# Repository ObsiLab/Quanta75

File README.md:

# Quanta75 Mechanical Keyboard - 75% ISO Layout
Playing around trying to design a custom keyboard  

#### Project advancement : [Quanta75's Github Project](https://github.com/orgs/ObsiLab/projects/2)  

## Documentation
Documentation about Quanta75 can be found on [the Quanta website: quanta.obsilab.com](https://quanta.obsilab.com).

## PCB
Quanta75 exists in multiple versions:
- RP2040 Stamp microcontroller board by Solder Party
  - General components
  - JLCPCB assembly service optimized BOM
- RPi Pico microcontroller board
  - General components
  - JLCPCB assembly service optimized components
- Bare RP2040 microcontroller chip
  - General components
  - JLCPCB assembly service optimized components

All of them are using SMD components but no smaller than 0603 and on hand-solderable pads (a complete through-hole PCB could be coming next 👀). A PCB assembly service is still recommended.

#### See the PCB and schematic in [KiCanvas' Browser PCB viewer](https://kicanvas.org/?github=https%3A%2F%2Fgithub.com%2FLucasPlacentino%2FQuanta%2Ftree%2Fmain%2FQuanta_RP2040Stamp_JLCPCBAoptimized).

## Firmware (_WIP_)

[rmk_firmware](https://github.com/ObsiLab/rmk_firmware) _WIP_  
RMK is a keyboard firmware written in Rust, inspired by QMK or KMK. Originally built for the Quanta.

QMK config for the Quanta: _WIP_  

VIA config for the Quanta: _WIP_  

VIAL config for the Quanta: _WIP_  

## Design :
See the design details [here](/design).

## License
Project licensed under [CERN-OHL-P v2](LICENSE).

> Logos are licensed under [CC BY-NC-ND 4.0 ](https://creativecommons.org/licenses/by-nc-nd/4.0/) (more info [here](/design/README.md)).

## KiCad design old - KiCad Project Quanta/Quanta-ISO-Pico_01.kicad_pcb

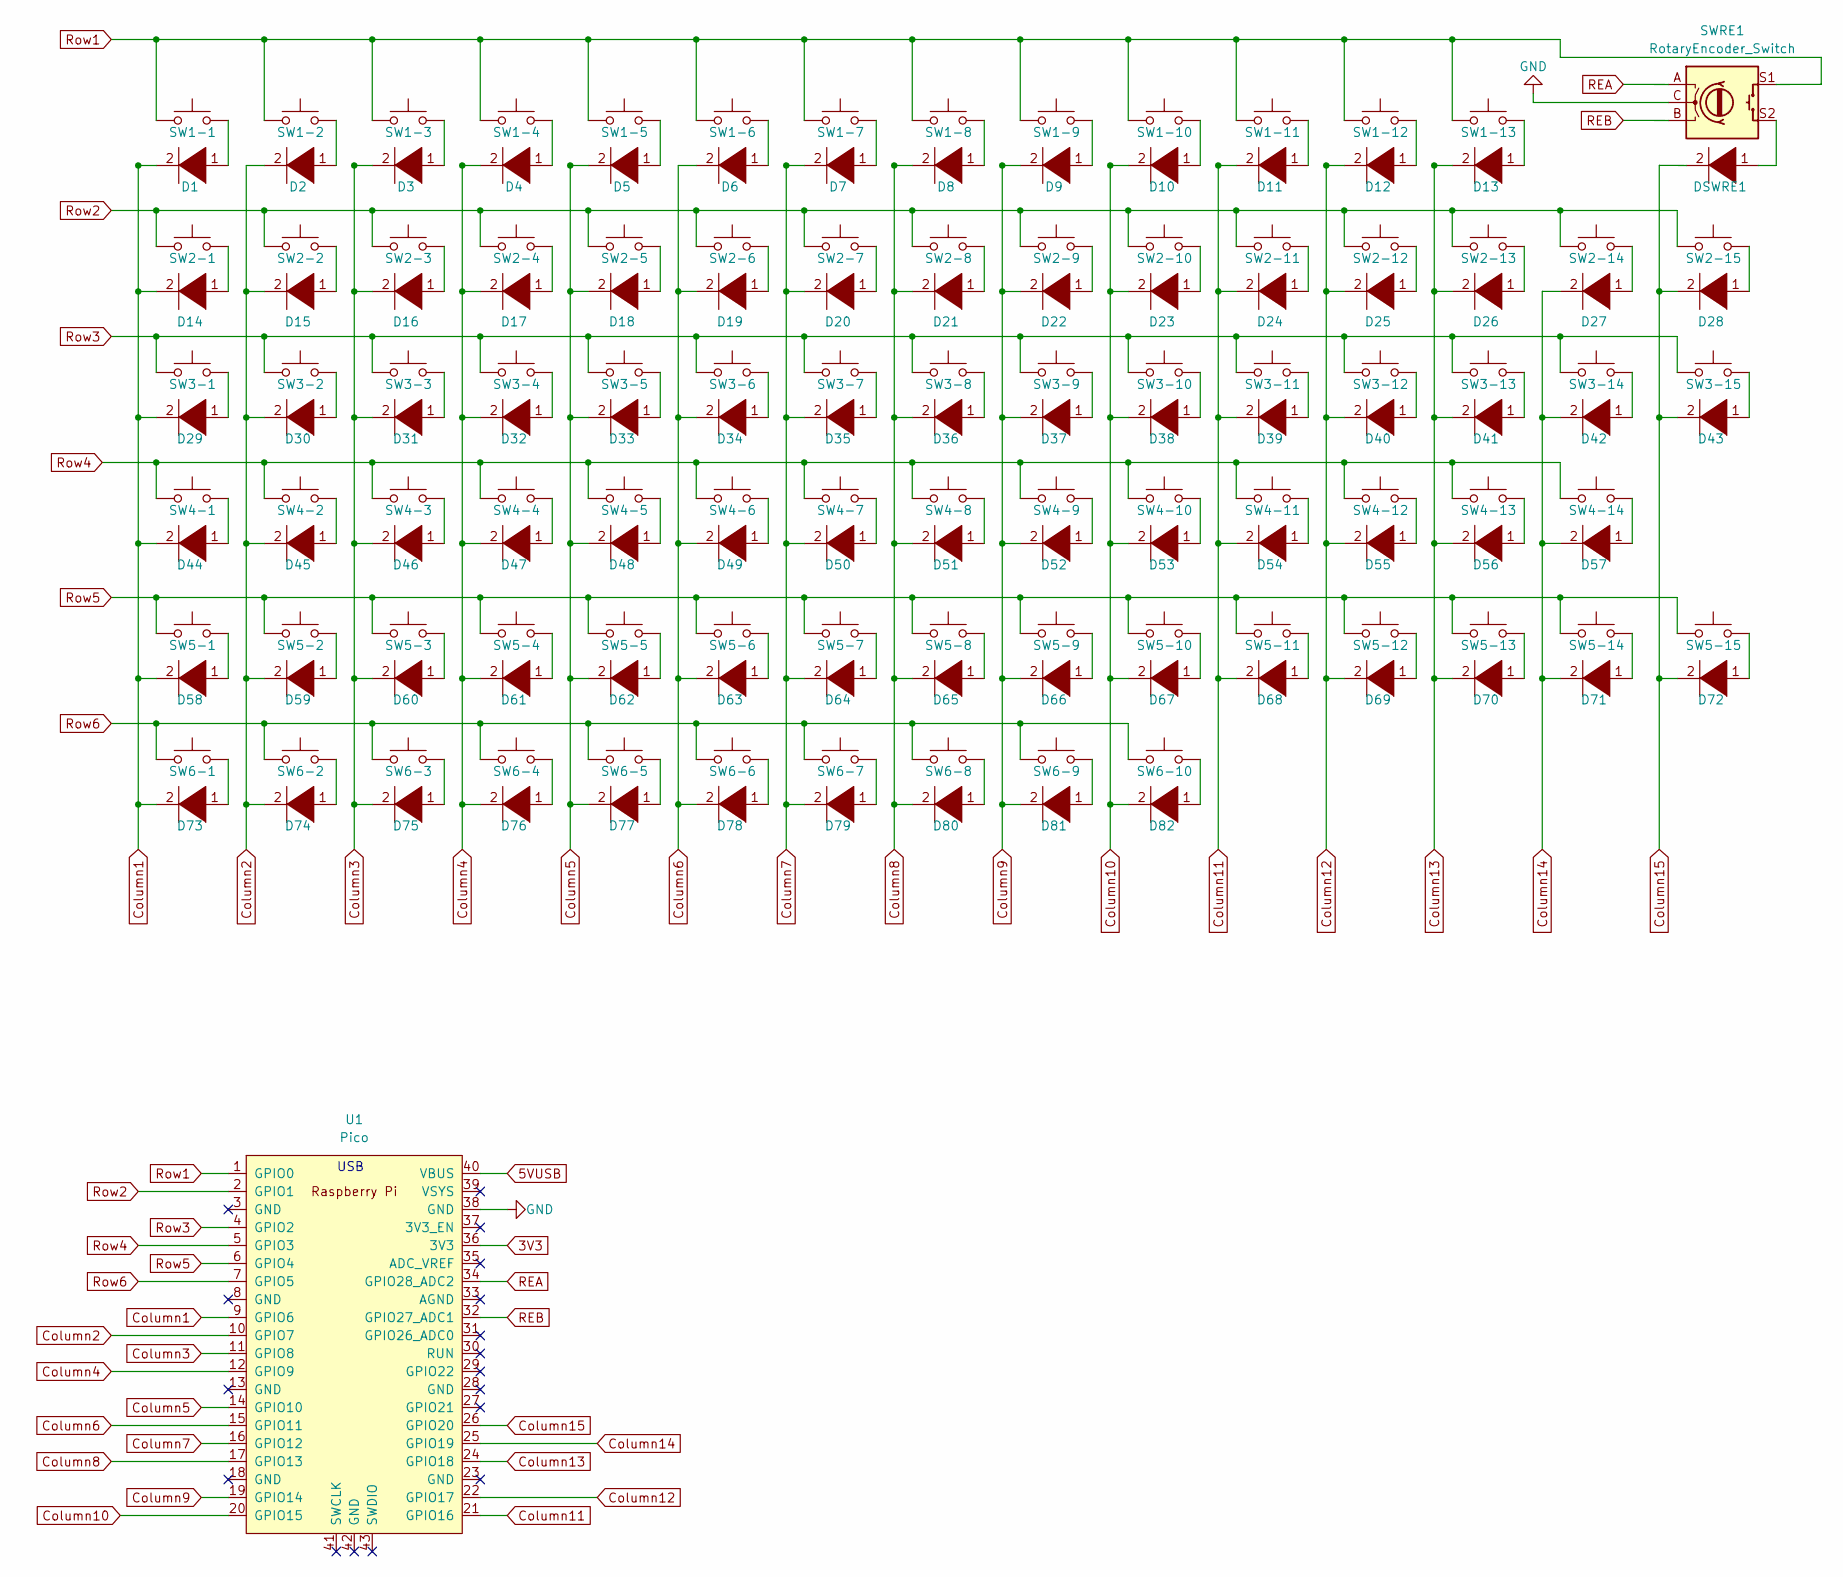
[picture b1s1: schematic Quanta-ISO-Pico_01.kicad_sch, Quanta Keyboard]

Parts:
D1, D2, D3, D4, D5, D6, D7, D8, D9, D10, D11, D12, D13, D14, D15, D16, D17, D18, D19, D20, D21, D22, D23, D24, D25, D26, D27, D28, D29, D30, D31, D32, D33, D34, D35, D36, D37, D38, D39, D40, D41, D42, D43, D44, D45, D46, D47, D48, D49, D50, D51, D52, D53, D54, D55, D56, D57, D58, D59, D60, D61, D62, D63, D64, D65, D66, D67, D68, D69, D70, D71, D72, D73, D74, D75, D76, D77, D78, D79, D80, D81, D82: DIODE; D_A-405_P7.62mm_Horizontal
DSWRE1: DIODE; D_A-405_P7.62mm_Horizontal
SW1-1, SW1-2, SW1-3, SW1-4, SW1-5, SW1-6, SW1-7, SW1-8, SW1-9, SW1-10, SW1-11, SW1-12, SW1-13, SW2-1, SW2-2, SW2-3, SW2-4, SW2-5, SW2-6, SW2-7, SW2-8, SW2-9, SW2-10, SW2-11, SW2-12, SW2-13, SW2-14, SW2-15, SW3-1, SW3-2, SW3-3, SW3-4, SW3-5, SW3-6, SW3-7, SW3-8, SW3-9, SW3-10, SW3-11, SW3-12, SW3-13, SW3-14, SW3-15, SW4-1, SW4-2, SW4-3, SW4-4, SW4-5, SW4-6, SW4-7, SW4-8, SW4-9, SW4-10, SW4-11, SW4-12, SW4-13, SW4-14, SW5-1, SW5-2, SW5-3, SW5-4, SW5-5, SW5-6, SW5-7, SW5-8, SW5-9, SW5-10, SW5-11, SW5-12, SW5-13, SW5-14, SW5-15, SW6-1, SW6-2, SW6-3, SW6-4, SW6-5, SW6-6, SW6-7, SW6-8, SW6-9, SW6-10: SW_Push; SW_Cherry_MX_1.00u_PCB
SWRE1: RotaryEncoder_Switch; RotaryEncoder_Bourns_Vertical_PEC12R-3xxxF-Sxxxx
U1: Pico; RPi_Pico_SMD_TH

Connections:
Column1: D1.2 (A), D14.2 (A), D29.2 (A), D44.2 (A), D58.2 (A), D73.2 (A), U1.9 (GPIO6)
Column2: D2.2 (A), D15.2 (A), D30.2 (A), D45.2 (A), D59.2 (A), D74.2 (A), U1.10 (GPIO7)
Column3: D3.2 (A), D16.2 (A), D31.2 (A), D46.2 (A), D60.2 (A), D75.2 (A), U1.11 (GPIO8)
Column4: D4.2 (A), D17.2 (A), D32.2 (A), D47.2 (A), D61.2 (A), D76.2 (A), U1.12 (GPIO9)
Column5: D5.2 (A), D18.2 (A), D33.2 (A), D48.2 (A), D62.2 (A), D77.2 (A), U1.14 (GPIO10)
Column6: D6.2 (A), D19.2 (A), D34.2 (A), D49.2 (A), D63.2 (A), D78.2 (A), U1.15 (GPIO11)
Column7: D7.2 (A), D20.2 (A), D35.2 (A), D50.2 (A), D64.2 (A), D79.2 (A), U1.16 (GPIO12)
Column8: D8.2 (A), D21.2 (A), D36.2 (A), D51.2 (A), D65.2 (A), D80.2 (A), U1.17 (GPIO13)
Column9: D9.2 (A), D22.2 (A), D37.2 (A), D52.2 (A), D66.2 (A), D81.2 (A), U1.19 (GPIO14)
Column10: D10.2 (A), D23.2 (A), D38.2 (A), D53.2 (A), D67.2 (A), D82.2 (A), U1.20 (GPIO15)
Column11: D11.2 (A), D24.2 (A), D39.2 (A), D54.2 (A), D68.2 (A), U1.21 (GPIO16)
Column12: D12.2 (A), D25.2 (A), D40.2 (A), D55.2 (A), D69.2 (A), U1.22 (GPIO17)
Column13: D13.2 (A), D26.2 (A), D41.2 (A), D56.2 (A), D70.2 (A), U1.24 (GPIO18)
Column14: D27.2 (A), D42.2 (A), D57.2 (A), D71.2 (A), U1.25 (GPIO19)
Column15: D28.2 (A), D43.2 (A), D72.2 (A), DSWRE1.2 (A), U1.26 (GPIO20)
GND: SWRE1.C, U1.38 (GND)
unnamed: D1.1 (K), SW1-1.2
unnamed: D2.1 (K), SW1-2.2
unnamed: D3.1 (K), SW1-3.2
unnamed: D4.1 (K), SW1-4.2
unnamed: D5.1 (K), SW1-5.2
unnamed: D6.1 (K), SW1-6.2
unnamed: D7.1 (K), SW1-7.2
unnamed: D8.1 (K), SW1-8.2
unnamed: D9.1 (K), SW1-9.2
unnamed: D10.1 (K), SW1-10.2
unnamed: D11.1 (K), SW1-11.2
unnamed: D12.1 (K), SW1-12.2
unnamed: D13.1 (K), SW1-13.2
unnamed: D14.1 (K), SW2-1.2
unnamed: D15.1 (K), SW2-2.2
unnamed: D16.1 (K), SW2-3.2
unnamed: D17.1 (K), SW2-4.2
unnamed: D18.1 (K), SW2-5.2
unnamed: D19.1 (K), SW2-6.2
unnamed: D20.1 (K), SW2-7.2
unnamed: D21.1 (K), SW2-8.2
unnamed: D22.1 (K), SW2-9.2
unnamed: D23.1 (K), SW2-10.2
unnamed: D24.1 (K), SW2-11.2
unnamed: D25.1 (K), SW2-12.2
unnamed: D26.1 (K), SW2-13.2
unnamed: D27.1 (K), SW2-14.2
unnamed: D28.1 (K), SW2-15.2
unnamed: D29.1 (K), SW3-1.2
unnamed: D30.1 (K), SW3-2.2
unnamed: D31.1 (K), SW3-3.2
unnamed: D32.1 (K), SW3-4.2
unnamed: D33.1 (K), SW3-5.2
unnamed: D34.1 (K), SW3-6.2
unnamed: D35.1 (K), SW3-7.2
unnamed: D36.1 (K), SW3-8.2
unnamed: D37.1 (K), SW3-9.2
unnamed: D38.1 (K), SW3-10.2
unnamed: D39.1 (K), SW3-11.2
unnamed: D40.1 (K), SW3-12.2
unnamed: D41.1 (K), SW3-13.2
unnamed: D42.1 (K), SW3-14.2
unnamed: D43.1 (K), SW3-15.2
unnamed: D44.1 (K), SW4-1.2
unnamed: D45.1 (K), SW4-2.2
unnamed: D46.1 (K), SW4-3.2
unnamed: D47.1 (K), SW4-4.2
unnamed: D48.1 (K), SW4-5.2
unnamed: D49.1 (K), SW4-6.2
unnamed: D50.1 (K), SW4-7.2
unnamed: D51.1 (K), SW4-8.2
unnamed: D52.1 (K), SW4-9.2
unnamed: D53.1 (K), SW4-10.2
unnamed: D54.1 (K), SW4-11.2
unnamed: D55.1 (K), SW4-12.2
unnamed: D56.1 (K), SW4-13.2
unnamed: D57.1 (K), SW4-14.2
unnamed: D58.1 (K), SW5-1.2
unnamed: D59.1 (K), SW5-2.2
unnamed: D60.1 (K), SW5-3.2
unnamed: D61.1 (K), SW5-4.2
unnamed: D62.1 (K), SW5-5.2
unnamed: D63.1 (K), SW5-6.2
unnamed: D64.1 (K), SW5-7.2
unnamed: D65.1 (K), SW5-8.2
unnamed: D66.1 (K), SW5-9.2
unnamed: D67.1 (K), SW5-10.2
unnamed: D68.1 (K), SW5-11.2
unnamed: D69.1 (K), SW5-12.2
unnamed: D70.1 (K), SW5-13.2
unnamed: D71.1 (K), SW5-14.2
unnamed: D72.1 (K), SW5-15.2
unnamed: D73.1 (K), SW6-1.2
unnamed: D74.1 (K), SW6-2.2
unnamed: D75.1 (K), SW6-3.2
unnamed: D76.1 (K), SW6-4.2
unnamed: D77.1 (K), SW6-5.2
unnamed: D78.1 (K), SW6-6.2
unnamed: D79.1 (K), SW6-7.2
unnamed: D80.1 (K), SW6-8.2
unnamed: D81.1 (K), SW6-9.2
unnamed: D82.1 (K), SW6-10.2
unnamed: DSWRE1.1 (K), SWRE1.S2
REA: SWRE1.A, U1.34 (GPIO28_ADC2)
REB: SWRE1.B, U1.32 (GPIO27_ADC1)
Row1: SW1-1.1, SW1-2.1, SW1-3.1, SW1-4.1, SW1-5.1, SW1-6.1, SW1-7.1, SW1-8.1, SW1-9.1, SW1-10.1, SW1-11.1, SW1-12.1, SW1-13.1, SWRE1.S1, U1.1 (GPIO0)
Row2: SW2-1.1, SW2-2.1, SW2-3.1, SW2-4.1, SW2-5.1, SW2-6.1, SW2-7.1, SW2-8.1, SW2-9.1, SW2-10.1, SW2-11.1, SW2-12.1, SW2-13.1, SW2-14.1, SW2-15.1, U1.2 (GPIO1)
Row3: SW3-1.1, SW3-2.1, SW3-3.1, SW3-4.1, SW3-5.1, SW3-6.1, SW3-7.1, SW3-8.1, SW3-9.1, SW3-10.1, SW3-11.1, SW3-12.1, SW3-13.1, SW3-14.1, SW3-15.1, U1.4 (GPIO2)
Row4: SW4-1.1, SW4-2.1, SW4-3.1, SW4-4.1, SW4-5.1, SW4-6.1, SW4-7.1, SW4-8.1, SW4-9.1, SW4-10.1, SW4-11.1, SW4-12.1, SW4-13.1, SW4-14.1, U1.5 (GPIO3)
Row5: SW5-1.1, SW5-2.1, SW5-3.1, SW5-4.1, SW5-5.1, SW5-6.1, SW5-7.1, SW5-8.1, SW5-9.1, SW5-10.1, SW5-11.1, SW5-12.1, SW5-13.1, SW5-14.1, SW5-15.1, U1.6 (GPIO4)
Row6: SW6-1.1, SW6-2.1, SW6-3.1, SW6-4.1, SW6-5.1, SW6-6.1, SW6-7.1, SW6-8.1, SW6-9.1, SW6-10.1, U1.7 (GPIO5)

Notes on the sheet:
USB

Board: 2 copper layers, 166 parts (0 on the bottom side), 104 nets, no tracks yet.

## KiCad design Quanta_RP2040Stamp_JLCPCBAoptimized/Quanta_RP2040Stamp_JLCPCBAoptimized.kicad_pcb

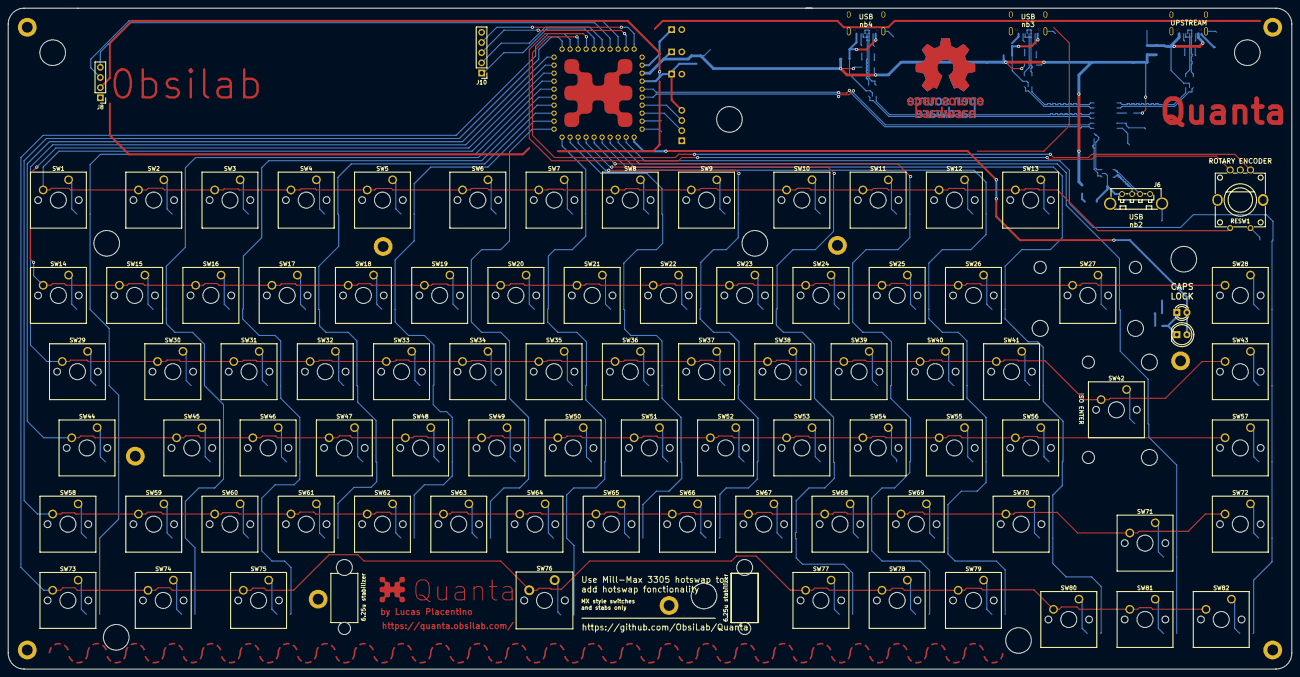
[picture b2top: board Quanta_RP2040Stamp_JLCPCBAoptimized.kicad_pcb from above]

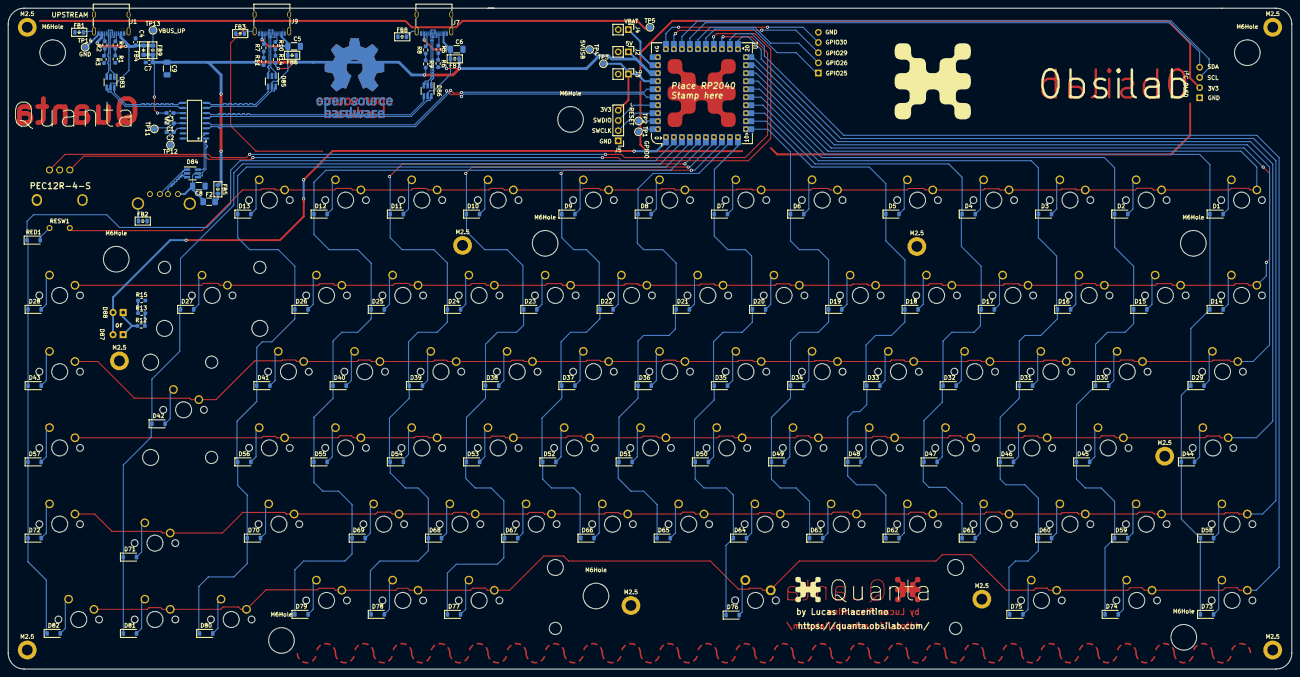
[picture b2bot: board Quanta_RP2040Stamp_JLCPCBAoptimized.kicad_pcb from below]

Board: 2 copper layers, 320.7 x 165.1 mm, 249 parts (140 on the bottom side), 162 nets.

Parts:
6.25u stabilizer: Stabilizer_Cherry_MX_6.25u
C1, C2, C4: 10uF; C_0603_1608Metric_Pad1.08x0.95mm_HandSolder
C3, C7: 100nF; C_0603_1608Metric_Pad1.08x0.95mm_HandSolder
C5, C6, C8, C9: 100uF; C_1206_3216Metric_Pad1.33x1.80mm_HandSolder
D1, D2, D3, D4, D5, D6, D7, D8, D9, D10, D11, D12, D13, D14, D15, D16, D17, D18, D19, D20, D21, D22, D23, D24, D25, D26, D27, D28, D29, D30, D31, D32, D33, D34, D35, D36, D37, D38, D39, D40, D41, D42, D43, D44, D45, D46, D47, D48, D49, D50, D51, D52, D53, D54, D55, D56, D57, D58, D59, D60, D61, D62, D63, D64, D65, D66, D67, D68, D69, D70, D71, D72, D73, D74, D75, D76, D77, D78, D79, D80, D81, D82: DIODE; D_SOD-123
D83, D84, D85, D86: USBLC6-2SC6; SOT-23-6_Handsoldering
D87: Amber LED; LED_D5.0mm_Clear
D88: Amber LED; LED_D3.0mm_Clear
F2: 500mA; Fuse_1206_3216Metric_Pad1.42x1.75mm_HandSolder
FB1, FB2, FB3, FB8: 600R; Ferrite_0805_2012Metric
FB4, FB9: 100R 800mA; Ferrite_0805_2012Metric_Pad1.05x1.20mm_BigPads
FB5, FB6, FB7: 600R 500mA; Ferrite_0805_2012Metric
J1, J7, J9: USB_C_Receptacle_USB2.0; USB-C-SMD_G-SWITCH_GT-USB-7010EN
J2: Conn_01x02_Socket VBUS 5V; PinHeader_1x02_P2.54mm_Vertical
J3: Conn_01x02_Socket 3V3; PinHeader_1x02_P2.54mm_Vertical
J4: Conn_01x02_Socket VBAT; PinHeader_1x02_P2.54mm_Vertical
J5: Conn_01x04_Socket SWD; PinHeader_1x04_P2.54mm_Vertical
J6: USB_A_Receptacle_UBS2.0; USB-A-TH_KH-AF180ZJ-13.7
J8: Conn_01x04_Socket I2C display; PinHeader_1x04_P2.54mm_Vertical
J10: Conn_01x05_Socket GPIOs; PinHeader_1x05_P2.54mm_Vertical
M2.5, M2.5#2, M2.5#3, M2.5#4, M2.5#5, M2.5#6, M2.5#7, M2.5#8, M2.5#9, M2.5#10: MountingHole_2.7mm_M2.5_DIN965_Pad
M6Hole, M6Hole#2, M6Hole#3, M6Hole#4, M6Hole#5, M6Hole#6, M6Hole#7, M6Hole#8, M6Hole#9: MountingHole_6.4mm_M6_DIN965
OSHW-logo: OSHW-Logo_19x20mm_Copper
Quanta***: LOGO; Quanta-logo
R1, R3, R12, R13, R15: 120R; R_0603_1608Metric_Pad0.98x0.95mm_HandSolder
R2, R4: 4k99; R_0603_1608Metric_Pad0.98x0.95mm_HandSolder
R5, R7, R8, R10: 43k; R_0603_1608Metric_Pad0.98x0.95mm_HandSolder
R6, R9, R11, R14: 15k; R_0603_1608Metric_Pad0.98x0.95mm_HandSolder
RED1: DIODE; D_SOD-123
RESW1: RotaryEncoder_Switch; SW-TH_PEC12R-4120F-S0012
SW1, SW2, SW3, SW4, SW5, SW6, SW7, SW8, SW9, SW10, SW11, SW12, SW13, SW14, SW15, SW16, SW17, SW18, SW19, SW20, SW21, SW22, SW23, SW24, SW25, SW26, SW28, SW30, SW31, SW32, SW33, SW34, SW35, SW36, SW37, SW38, SW39, SW40, SW41, SW43, SW45, SW46, SW47, SW48, SW49, SW50, SW51, SW52, SW53, SW54, SW55, SW56, SW57, SW59, SW60, SW61, SW62, SW63, SW64, SW65, SW66, SW67, SW68, SW69, SW71, SW72, SW77, SW78, SW79, SW80, SW81, SW82: SW_Push; SW_Cherry_MX_1.00u_PCB
SW27: SW_Push; SW_Cherry_MX_2.00u_PCB
SW29: SW_Push; SW_Cherry_MX_1.50u_PCB
SW42: SW_Push; SW_Cherry_MX_ISOEnter_PCB
SW44, SW70: SW_Push; SW_Cherry_MX_1.75u_PCB
SW58, SW73, SW74, SW75: SW_Push; SW_Cherry_MX_1.25u_PCB
SW76: SW_Push; SW_Cherry_MX_PCB_6.25u
TP1: BOOTSEL; TestPoint_Pad_D1.5mm
TP2: -RESET; TestPoint_Pad_D1.5mm
TP3: 3V3; TestPoint_Pad_D1.5mm
TP4: 5VUSB; TestPoint_Pad_D1.5mm
TP5, TP14: GND; TestPoint_Pad_D1.5mm
TP11: VDD3; TestPoint_Pad_D1.5mm
TP12: VDD18; TestPoint_Pad_D1.5mm
TP13: VBUS_UP; TestPoint_Pad_D1.5mm
U1: RP2040_Stamp; RP2040_Stamp_THT
U2: SL2.1A; SOP-16_L10.0-W3.9-P1.27-LS6.0-BL

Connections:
+3.3V: J3.1, J5.4, J8.2, TP3.1, U1.34 (3.3V)
+5V: C3.2, C7.2, C9.2, FB4.2, FB5.1, FB6.1, FB7.1, FB9.2, J2.1, R6.2, R9.2, R11.2, R14.2, TP4.1, U1.33 (5V)
/USB2+: D84.1 (L1), J6.3 (D+)
/USB2-: D84.3 (L2), J6.2 (D-)
/USB3+: D85.3 (L2), J9.A6 (D+), J9.B6 (D+)
/USB3-: D85.1 (L1), J9.A7 (D-), J9.B7 (D-)
/USB4+: D86.3 (L2), J7.A6 (D+), J7.B6 (D+)
/USB4-: D86.1 (L1), J7.A7 (D-), J7.B7 (D-)
/USBUP+: D83.4 (L2), U2.10 (DP)
/USBUP-: D83.6 (L1), U2.9 (DM)
Column1: D1.1 (K), D14.1 (K), D29.1 (K), D44.1 (K), D58.1 (K), D73.1 (K), U1.16 (GPIO15)
Column2: D2.1 (K), D15.1 (K), D30.1 (K), D45.1 (K), D59.1 (K), D74.1 (K), U1.15 (GPIO14)
Column3: D3.1 (K), D16.1 (K), D31.1 (K), D46.1 (K), D60.1 (K), D75.1 (K), U1.14 (GPIO13)
Column4: D4.1 (K), D17.1 (K), D32.1 (K), D47.1 (K), D61.1 (K), U1.13 (GPIO12)
Column5: D5.1 (K), D18.1 (K), D33.1 (K), D48.1 (K), D62.1 (K), U1.12 (GPIO11)
Column6: D6.1 (K), D19.1 (K), D34.1 (K), D49.1 (K), D63.1 (K), U1.11 (GPIO10)
Column7: D7.1 (K), D20.1 (K), D35.1 (K), D50.1 (K), D64.1 (K), D76.1 (K), U1.10 (GPIO9)
Column8: D8.1 (K), D21.1 (K), D36.1 (K), D51.1 (K), D65.1 (K), U1.9 (GPIO8)
Column9: D9.1 (K), D22.1 (K), D37.1 (K), D52.1 (K), D66.1 (K), U1.8 (GPIO7)
Column10: D10.1 (K), D23.1 (K), D38.1 (K), D53.1 (K), D67.1 (K), D77.1 (K), U1.7 (GPIO6)
Column11: D11.1 (K), D24.1 (K), D39.1 (K), D54.1 (K), D68.1 (K), D78.1 (K), U1.6 (GPIO5)
Column12: D12.1 (K), D25.1 (K), D40.1 (K), D55.1 (K), D69.1 (K), D79.1 (K), U1.5 (GPIO4)
Column13: D13.1 (K), D26.1 (K), D41.1 (K), D56.1 (K), D70.1 (K), D80.1 (K), U1.4 (GPIO3)
Column14: D27.1 (K), D42.1 (K), D71.1 (K), D81.1 (K), U1.3 (GPIO2)
Column15: D28.1 (K), D43.1 (K), D57.1 (K), D72.1 (K), D82.1 (K), RED1.1 (K), U1.2 (GPIO1)
GND: C1.2, C2.2, C4.1, C5.2, C6.2, C7.1, C8.1, C9.1, D83.2 (VN), D84.2 (VN), D85.2 (VN), D86.2 (VN), FB1.1, FB2.1, FB3.1, FB8.1, J1.A1 (GND), J1.B1 (GND), J2.2, J3.2, J4.2, J5.1, J6.4 (GND), J7.A1 (GND), J7.B1 (GND), J8.1, J9.A1 (GND), J9.B1 (GND), J10.5, R1.2, R3.2, R15.2, RESW1.C, TP5.1, TP14.1, U1.31 (GND), U2.12 (GND), U2.16 (XIN)
GPIO0_LED: D87.2 (A), D88.2 (A), U1.1 (GPIO0)
I2C1-SCL: J8.3, U1.28 (GPIO27)
I2C1-SDA: J8.4, U1.27 (GPIO26)
unnamed: D1.2 (A), SW1.1
unnamed: D2.2 (A), SW2.1
unnamed: D3.2 (A), SW3.1
unnamed: D4.2 (A), SW4.1
unnamed: D5.2 (A), SW5.1
unnamed: D6.2 (A), SW6.1
unnamed: D7.2 (A), SW7.1
unnamed: D8.2 (A), SW8.1
unnamed: D9.2 (A), SW9.1
unnamed: D10.2 (A), SW10.1
unnamed: D11.2 (A), SW11.1
unnamed: D12.2 (A), SW12.1
unnamed: D13.2 (A), SW13.1
unnamed: D14.2 (A), SW14.1
unnamed: D15.2 (A), SW15.1
unnamed: D16.2 (A), SW16.1
unnamed: D17.2 (A), SW17.1
unnamed: D18.2 (A), SW18.1
unnamed: D19.2 (A), SW19.1
unnamed: D20.2 (A), SW20.1
unnamed: D21.2 (A), SW21.1
unnamed: D22.2 (A), SW22.1
unnamed: D23.2 (A), SW23.1
unnamed: D24.2 (A), SW24.1
unnamed: D25.2 (A), SW25.1
unnamed: D26.2 (A), SW26.1
unnamed: D27.2 (A), SW27.1
unnamed: D28.2 (A), SW28.1
unnamed: D29.2 (A), SW29.1
unnamed: D30.2 (A), SW30.1
unnamed: D31.2 (A), SW31.1
unnamed: D32.2 (A), SW32.1
unnamed: D33.2 (A), SW33.1
unnamed: D34.2 (A), SW34.1
unnamed: D35.2 (A), SW35.1
unnamed: D36.2 (A), SW36.1
unnamed: D37.2 (A), SW37.1
unnamed: D38.2 (A), SW38.1
unnamed: D39.2 (A), SW39.1
unnamed: D40.2 (A), SW40.1
unnamed: D41.2 (A), SW41.1
unnamed: D42.2 (A), SW42.1
unnamed: D43.2 (A), SW43.1
unnamed: D44.2 (A), SW44.1
unnamed: D45.2 (A), SW45.1
unnamed: D46.2 (A), SW46.1
unnamed: D47.2 (A), SW47.1
unnamed: D48.2 (A), SW48.1
unnamed: D49.2 (A), SW49.1
unnamed: D50.2 (A), SW50.1
unnamed: D51.2 (A), SW51.1
unnamed: D52.2 (A), SW52.1
unnamed: D53.2 (A), SW53.1
unnamed: D54.2 (A), SW54.1
unnamed: D55.2 (A), SW55.1
unnamed: D56.2 (A), SW56.1
unnamed: D57.2 (A), SW57.1
unnamed: D58.2 (A), SW58.1
unnamed: D59.2 (A), SW59.1
unnamed: D60.2 (A), SW60.1
unnamed: D61.2 (A), SW61.1
unnamed: D62.2 (A), SW62.1
unnamed: D63.2 (A), SW63.1
unnamed: D64.2 (A), SW64.1
unnamed: D65.2 (A), SW65.1
unnamed: D66.2 (A), SW66.1
unnamed: D67.2 (A), SW67.1
unnamed: D68.2 (A), SW68.1
unnamed: D69.2 (A), SW69.1
unnamed: D70.2 (A), SW70.1
unnamed: D71.2 (A), SW71.1
unnamed: D72.2 (A), SW72.1
unnamed: D73.2 (A), SW73.1
unnamed: D74.2 (A), SW74.1
unnamed: D75.2 (A), SW75.1
unnamed: D76.2 (A), SW76.2
unnamed: D77.2 (A), SW77.1
unnamed: D78.2 (A), SW78.1
unnamed: D79.2 (A), SW79.1
unnamed: D80.2 (A), SW80.1
unnamed: D81.2 (A), SW81.1
unnamed: D82.2 (A), SW82.1
unnamed: C8.2, D84.5 (VP), F2.1, FB5.2, J6.1 (VBUS)
unnamed: C5.1, D85.5 (VP), FB6.2, J9.A4 (VBUS), J9.B4 (VBUS)
unnamed: C6.1, D86.5 (VP), FB7.2, J7.A4 (VBUS), J7.B4 (VBUS)
unnamed: D87.1 (K), D88.1 (K), R12.1
unnamed: J1.A5 (CC1), R4.1
unnamed: J1.B5 (CC2), R2.1
unnamed: J5.2, U1.38 (SWCLK)
unnamed: J5.3, U1.37 (SWDIO)
unnamed: FB2.2, J6.5 (Shield)
unnamed: J7.A5 (CC1), R5.1
unnamed: J7.B5 (CC2), R8.1
unnamed: FB8.2, J7.2
unnamed: J9.A5 (CC1), R10.1
unnamed: J9.B5 (CC2), R7.1
unnamed: J10.1, U1.25 (GPIO24)
unnamed: J10.2, U1.26 (GPIO25)
unnamed: J10.3, U1.29 (GPIO28)
unnamed: J10.4, U1.30 (GPIO29)
unnamed: R1.1, R4.2
unnamed: R2.2, R3.1
unnamed: R5.2, R6.1
unnamed: R8.2, R9.1
unnamed: R10.2, R14.1
unnamed: R7.2, R11.1
unnamed: R12.2, R13.1
unnamed: R13.2, R15.1
unnamed: TP1.1, U1.40 (BOOTSEL)
unnamed: TP2.1, U1.39 (~RESET)
unnamed: C3.1, U2.11 (VDD5)
unnamed: C2.1, TP12.1, U2.14 (VDD18)
unnamed: C1.1, TP11.1, U2.13 (VDD33)
REA: RESW1.A, U1.23 (GPIO22)
REB: RESW1.B, U1.24 (GPIO23)
Row1: SW1.2, SW2.2, SW3.2, SW4.2, SW5.2, SW6.2, SW7.2, SW8.2, SW9.2, SW10.2, SW11.2, SW12.2, SW13.2, U1.17 (GPIO16)
Row2: SW14.2, SW15.2, SW16.2, SW17.2, SW18.2, SW19.2, SW20.2, SW21.2, SW22.2, SW23.2, SW24.2, SW25.2, SW26.2, SW27.2, SW28.2, U1.18 (GPIO17)
Row3: SW29.2, SW30.2, SW31.2, SW32.2, SW33.2, SW34.2, SW35.2, SW36.2, SW37.2, SW38.2, SW39.2, SW40.2, SW41.2, SW42.2, SW43.2, U1.19 (GPIO18)
Row4: SW44.2, SW45.2, SW46.2, SW47.2, SW48.2, SW49.2, SW50.2, SW51.2, SW52.2, SW53.2, SW54.2, SW55.2, SW56.2, SW57.2, U1.20 (GPIO19)
Row5: SW58.2, SW59.2, SW60.2, SW61.2, SW62.2, SW63.2, SW64.2, SW65.2, SW66.2, SW67.2, SW68.2, SW69.2, SW70.2, SW71.2, SW72.2, U1.21 (GPIO20)
Row6: SW73.2, SW74.2, SW75.2, SW76.1, SW77.2, SW78.2, SW79.2, SW80.2, SW81.2, SW82.2, U1.22 (GPIO21)
USB1_D+: U1.36 (USB_D+), U2.4 (DP3)
USB1_D-: U1.35 (USB_D-), U2.3 (DM3)
USB2_D+: D84.6 (L1), U2.2 (DP4)
USB2_D-: D84.4 (L2), U2.1 (DM4)
USB3_D+: D85.4 (L2), U2.8 (DP1)
USB3_D-: D85.6 (L1), U2.7 (DM1)
USB4_D+: D86.4 (L2), U2.6 (DP2)
USB4_D-: D86.6 (L1), U2.5 (DM2)
USB_UP_D+: D83.3 (L2), J1.A6 (D+), J1.B6 (D+)
USB_UP_D-: D83.1 (L1), J1.A7 (D-), J1.B7 (D-)
VBAT: J4.1, U1.32 (VBAT)
VBUS_UP: C4.2, D83.5 (VP), FB4.1, FB9.1, J1.A4 (VBUS), J1.B4 (VBUS), TP13.1

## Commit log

2021-06-15 Update issue templates
2021-07-23 Set theme jekyll-theme-minimal
2021-07-23 test
2022-02-17 changed license
    changed license to Apache License Version 2.0
2022-06-04 changed license to CERN-OHL-P v2
    hardware focused open-source license
2022-06-04 added license statement
2022-07-11 Added v01 schem
    key and diode matrix + Pico schematic
2022-07-11 made with KLE
    http://www.keyboard-layout-editor.com/##@_backcolor=%23adacac&background_name=ABS%20WA&style=background-image%2F:%20url('%2F%2Fbg%2F%2Fplastic%2F%2Fabs-wa.jpg')%2F%3B&$$hashKey=086%3B&radii=15px&swit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
2022-07-11 added logo
2022-07-11 added logos
2022-07-11 logo explanation and layout
2022-07-11 added image assets to site
2022-07-11 Create CNAME
2022-07-12 filling up the website
2022-07-12 fixed favicon
2022-07-12 fix home page permalink
2022-07-12 index fix 2
2022-07-12 index fix 3
2022-07-12 index fix 4
2022-07-12 index fix 5
2022-07-12 test fix index
2022-07-12 test fix index 2
2022-07-12 index test fix 3
2022-07-12 test fix index 4
2022-07-12 test fml
2022-07-12 test fml 2
2022-07-14 gitignore
2022-07-14 test fix index fml
2022-07-14 test fix index fml 2
2022-07-14 test fix index fml 3
2022-07-14 test fix index fml 4
2022-07-14 test fix index fml 5
2022-07-14 test fix index fml 6 final maybe
2022-07-14 test fix index fml 7
2022-07-14 test n463413651616155
    pls
2022-07-14 test fix index n46846546
    plssss just work
2022-07-14 pls just work already
2022-07-14 index fix finally ?
    changed defaults for pages:
    - scope :
    path : "_pages"
2022-07-14 updated logo
2022-07-14 updated logo in readme
2022-07-15 fixed and updated website
2022-07-15 fixed image asset relative path
2022-07-17 fixed apple favicon
2022-11-13 add footprints as git submodules
2023-01-18 readme typo
2023-04-21 add gradient logo text
2023-06-13 new kicad project
2023-06-13 start pcb
2023-06-13 backup
2023-06-13 removed JST connectors for USBs
2023-06-13 rename kicad project
2023-06-14 optimize cost for JLCPCB assembly service
2023-06-14 update rev of optimized pcb
2023-06-14 routed matrix for optimized version
2023-06-14 finished optimized pcb
2023-06-14 changed logo license
2023-06-14 fine tune optimized pcb
2023-06-14 added draft zone fills
2023-06-15 cleanup
2023-06-15 added teardrops
2023-06-20 add Bare RP2040 schematic
2023-06-20 add spst switch to bare rp2040 schematic
2023-06-20 update net label
2023-06-21 update font
2023-06-21 rename to Quanta75
2023-06-21 Update logo and font
2023-06-21 renamed everything to Quanta75
2023-06-21 additional screw holes
2023-06-21 small update
2023-06-21 link 3D models
2023-06-29 add oshw logo
    OSHW BE10
2023-07-08 update pcb
2023-07-08 finalized rp2040 version placements
2023-07-11 finalize routing
2023-07-11 copper fill gnd plane
2024-03-01 Update to KiCad 8.0
    plus few very minor fixes: missing silkscreen text, mispositioned decorative pad
2024-05-28 [ImgBot] Optimize images
    *Total -- 4,271.43kb -> 3,370.45kb (21.09%)
    /docs/assets/images/RMKlogo.png -- 31.22kb -> 11.04kb (64.65%)
    /design/keyboard-layout-qwerty.png -- 35.58kb -> 12.58kb (64.64%)
    /docs/assets/images/RMKtextlogo.png -- 105.63kb -> 51.10kb (51.62%)
    /oshw-BE000010-Quanta.png -- 17.48kb -> 9.41kb (46.18%)
    /docs/assets/images/firmware_code.png -- 192.06kb -> 127.79kb (33.46%)
